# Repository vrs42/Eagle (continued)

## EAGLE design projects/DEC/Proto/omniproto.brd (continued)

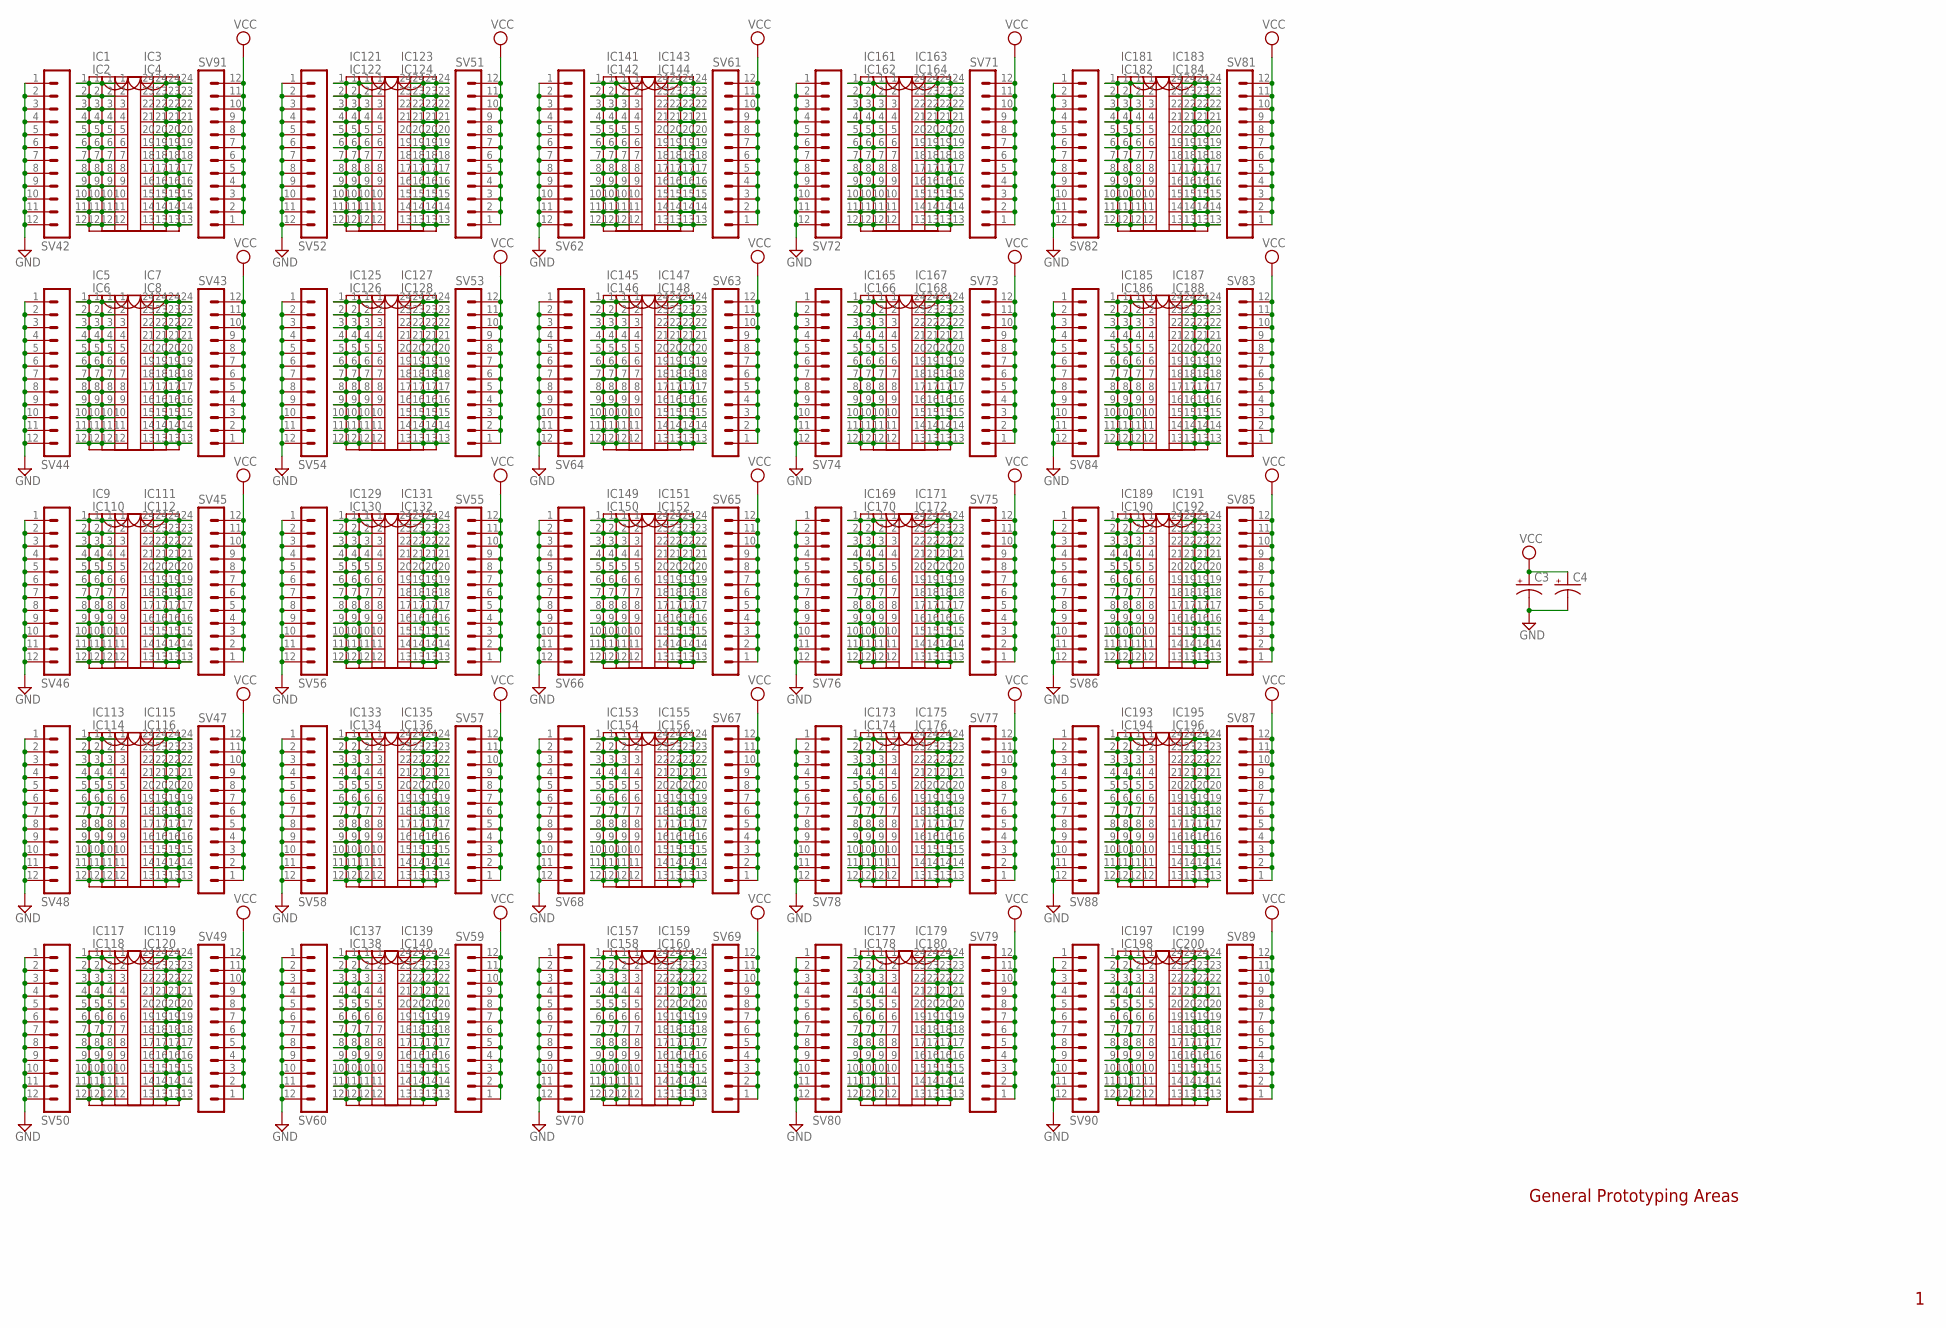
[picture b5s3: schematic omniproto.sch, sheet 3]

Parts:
C3, C4: CPOL-USE20-8AXIAL; E12-8
IC1, IC5, IC9, IC113, IC117, IC121, IC125, IC129, IC133, IC137, IC141, IC145, IC149, IC153, IC157, IC161, IC165, IC169, IC173, IC177, IC181, IC185, IC189, IC193, IC197: DIL24-3
IC2, IC4, IC6, IC8, IC110, IC112, IC114, IC116, IC118, IC120, IC122, IC124, IC126, IC128, IC130, IC132, IC134, IC136, IC138, IC140, IC142, IC144, IC146, IC148, IC150, IC152, IC154, IC156, IC158, IC160, IC162, IC164, IC166, IC168, IC170, IC172, IC174, IC176, IC178, IC180, IC182, IC184, IC186, IC188, IC190, IC192, IC194, IC196, IC198, IC200: DIL24-6
IC3, IC7, IC111, IC115, IC119, IC123, IC127, IC131, IC135, IC139, IC143, IC147, IC151, IC155, IC159, IC163, IC167, IC171, IC175, IC179, IC183, IC187, IC191, IC195, IC199: DIL24-9
SV42, SV43, SV44, SV45, SV46, SV47, SV48, SV49, SV50, SV51, SV52, SV53, SV54, SV55, SV56, SV57, SV58, SV59, SV60, SV61, SV62, SV63, SV64, SV65, SV66, SV67, SV68, SV69, SV70, SV71, SV72, SV73, SV74, SV75, SV76, SV77, SV78, SV79, SV80, SV81, SV82, SV83, SV84, SV85, SV86, SV87, SV88, SV89, SV90, SV91: MA12-1

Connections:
GND: C3.-, C4.-, SV42.1, SV42.2, SV42.3, SV42.4, SV42.5, SV42.6, SV42.7, SV42.8, SV42.9, SV42.10, SV42.11, SV42.12, SV44.1, SV44.2, SV44.3, SV44.4, SV44.5, SV44.6, SV44.7, SV44.8, SV44.9, SV44.10, SV44.11, SV44.12, SV46.1, SV46.2, SV46.3, SV46.4, SV46.5, SV46.6, SV46.7, SV46.8, SV46.9, SV46.10, SV46.11, SV46.12, SV48.1, SV48.2, SV48.3, SV48.4, SV48.5, SV48.6, SV48.7, SV48.8, SV48.9, SV48.10, SV48.11, SV48.12, SV50.1, SV50.2, SV50.3, SV50.4, SV50.5, SV50.6, SV50.7, SV50.8, SV50.9, SV50.10, SV50.11, SV50.12, SV52.1, SV52.2, SV52.3, SV52.4, SV52.5, SV52.6, SV52.7, SV52.8, SV52.9, SV52.10, SV52.11, SV52.12, SV54.1, SV54.2, SV54.3, SV54.4, SV54.5, SV54.6, SV54.7, SV54.8, SV54.9, SV54.10, SV54.11, SV54.12, SV56.1, SV56.2, SV56.3, SV56.4, SV56.5, SV56.6, SV56.7, SV56.8, SV56.9, SV56.10, SV56.11, SV56.12, SV58.1, SV58.2, SV58.3, SV58.4, SV58.5, SV58.6, SV58.7, SV58.8, SV58.9, SV58.10, SV58.11, SV58.12, SV60.1, SV60.2, SV60.3, SV60.4, SV60.5, SV60.6, SV60.7, SV60.8, SV60.9, SV60.10, SV60.11, SV60.12, SV62.1, SV62.2, SV62.3, SV62.4, SV62.5, SV62.6, SV62.7, SV62.8, SV62.9, SV62.10, SV62.11, SV62.12, SV64.1, SV64.2, SV64.3, SV64.4, SV64.5, SV64.6, SV64.7, SV64.8, SV64.9, SV64.10, SV64.11, SV64.12, SV66.1, SV66.2, SV66.3, SV66.4, SV66.5, SV66.6, SV66.7, SV66.8, SV66.9, SV66.10, SV66.11, SV66.12, SV68.1, SV68.2, SV68.3, SV68.4, SV68.5, SV68.6, SV68.7, SV68.8, SV68.9, SV68.10, SV68.11, SV68.12, SV70.1, SV70.2, SV70.3, SV70.4, SV70.5, SV70.6, SV70.7, SV70.8, SV70.9, SV70.10, SV70.11, SV70.12, SV72.1, SV72.2, SV72.3, SV72.4, SV72.5, SV72.6, SV72.7, SV72.8, SV72.9, SV72.10, SV72.11, SV72.12, SV74.1, SV74.2, SV74.3, SV74.4, SV74.5, SV74.6, SV74.7, SV74.8, SV74.9, SV74.10, SV74.11, SV74.12, SV76.1, SV76.2, SV76.3, SV76.4, SV76.5, SV76.6, SV76.7, SV76.8, SV76.9, SV76.10, SV76.11, SV76.12, SV78.1, SV78.2, SV78.3, SV78.4, SV78.5, SV78.6, SV78.7, SV78.8, SV78.9, SV78.10, SV78.11, SV78.12, SV80.1, SV80.2, SV80.3, SV80.4, SV80.5, SV80.6, SV80.7, SV80.8, SV80.9, SV80.10, SV80.11, SV80.12, SV82.1, SV82.2, SV82.3, SV82.4, SV82.5, SV82.6, SV82.7, SV82.8, SV82.9, SV82.10, SV82.11, SV82.12, SV84.1, SV84.2, SV84.3, SV84.4, SV84.5, SV84.6, SV84.7, SV84.8, SV84.9, SV84.10, SV84.11, SV84.12, SV86.1, SV86.2, SV86.3, SV86.4, SV86.5, SV86.6, SV86.7, SV86.8, SV86.9, SV86.10, SV86.11, SV86.12, SV88.1, SV88.2, SV88.3, SV88.4, SV88.5, SV88.6, SV88.7, SV88.8, SV88.9, SV88.10, SV88.11, SV88.12, SV90.1, SV90.2, SV90.3, SV90.4, SV90.5, SV90.6, SV90.7, SV90.8, SV90.9, SV90.10, SV90.11, SV90.12; also elsewhere on the board
unnamed: IC1.1, IC2.1, IC3.1, IC4.1
unnamed: IC1.2, IC2.2, IC3.2, IC4.2
unnamed: IC1.3, IC2.3, IC3.3, IC4.3
unnamed: IC1.4, IC2.4, IC3.4, IC4.4
unnamed: IC1.5, IC2.5, IC3.5, IC4.5
unnamed: IC1.6, IC2.6, IC3.6, IC4.6
unnamed: IC1.7, IC2.7, IC3.7, IC4.7
unnamed: IC1.8, IC2.8, IC3.8, IC4.8
unnamed: IC1.9, IC2.9, IC3.9, IC4.9
unnamed: IC1.10, IC2.10, IC3.10, IC4.10
unnamed: IC1.11, IC2.11, IC3.11, IC4.11
unnamed: IC1.12, IC2.12, IC3.12, IC4.12
unnamed: IC1.13, IC2.13, IC3.13, IC4.13
unnamed: IC1.14, IC2.14, IC3.14, IC4.14
unnamed: IC1.15, IC2.15, IC3.15, IC4.15
unnamed: IC1.16, IC2.16, IC3.16, IC4.16
unnamed: IC1.17, IC2.17, IC3.17, IC4.17
unnamed: IC1.18, IC2.18, IC3.18, IC4.18
unnamed: IC1.19, IC2.19, IC3.19, IC4.19
unnamed: IC1.20, IC2.20, IC3.20, IC4.20
unnamed: IC1.21, IC2.21, IC3.21, IC4.21
unnamed: IC1.22, IC2.22, IC3.22, IC4.22
unnamed: IC1.23, IC2.23, IC3.23, IC4.23
unnamed: IC1.24, IC2.24, IC3.24, IC4.24
unnamed: IC5.1, IC6.1, IC7.1, IC8.1
unnamed: IC5.2, IC6.2, IC7.2, IC8.2
unnamed: IC5.3, IC6.3, IC7.3, IC8.3
unnamed: IC5.4, IC6.4, IC7.4, IC8.4
unnamed: IC5.5, IC6.5, IC7.5, IC8.5
unnamed: IC5.6, IC6.6, IC7.6, IC8.6
unnamed: IC5.7, IC6.7, IC7.7, IC8.7
unnamed: IC5.8, IC6.8, IC7.8, IC8.8
unnamed: IC5.9, IC6.9, IC7.9, IC8.9
unnamed: IC5.10, IC6.10, IC7.10, IC8.10
unnamed: IC5.11, IC6.11, IC7.11, IC8.11
unnamed: IC5.12, IC6.12, IC7.12, IC8.12
unnamed: IC5.13, IC6.13, IC7.13, IC8.13
unnamed: IC5.14, IC6.14, IC7.14, IC8.14
unnamed: IC5.15, IC6.15, IC7.15, IC8.15
unnamed: IC5.16, IC6.16, IC7.16, IC8.16
unnamed: IC5.17, IC6.17, IC7.17, IC8.17
unnamed: IC5.18, IC6.18, IC7.18, IC8.18
unnamed: IC5.19, IC6.19, IC7.19, IC8.19
unnamed: IC5.20, IC6.20, IC7.20, IC8.20
unnamed: IC5.21, IC6.21, IC7.21, IC8.21
unnamed: IC5.22, IC6.22, IC7.22, IC8.22
unnamed: IC5.23, IC6.23, IC7.23, IC8.23
unnamed: IC5.24, IC6.24, IC7.24, IC8.24
unnamed: IC9.1, IC110.1, IC111.1, IC112.1
unnamed: IC9.2, IC110.2, IC111.2, IC112.2
unnamed: IC9.3, IC110.3, IC111.3, IC112.3
unnamed: IC9.4, IC110.4, IC111.4, IC112.4
unnamed: IC9.5, IC110.5, IC111.5, IC112.5
unnamed: IC9.6, IC110.6, IC111.6, IC112.6
unnamed: IC9.7, IC110.7, IC111.7, IC112.7
unnamed: IC9.8, IC110.8, IC111.8, IC112.8
unnamed: IC9.9, IC110.9, IC111.9, IC112.9
unnamed: IC9.10, IC110.10, IC111.10, IC112.10
unnamed: IC9.11, IC110.11, IC111.11, IC112.11
unnamed: IC9.12, IC110.12, IC111.12, IC112.12
unnamed: IC9.13, IC110.13, IC111.13, IC112.13
unnamed: IC9.14, IC110.14, IC111.14, IC112.14
unnamed: IC9.15, IC110.15, IC111.15, IC112.15
unnamed: IC9.16, IC110.16, IC111.16, IC112.16
unnamed: IC9.17, IC110.17, IC111.17, IC112.17
unnamed: IC9.18, IC110.18, IC111.18, IC112.18
unnamed: IC9.19, IC110.19, IC111.19, IC112.19
unnamed: IC9.20, IC110.20, IC111.20, IC112.20
unnamed: IC9.21, IC110.21, IC111.21, IC112.21
unnamed: IC9.22, IC110.22, IC111.22, IC112.22
unnamed: IC9.23, IC110.23, IC111.23, IC112.23
unnamed: IC9.24, IC110.24, IC111.24, IC112.24
unnamed: IC113.1, IC114.1, IC115.1, IC116.1
unnamed: IC113.2, IC114.2, IC115.2, IC116.2
unnamed: IC113.3, IC114.3, IC115.3, IC116.3
unnamed: IC113.4, IC114.4, IC115.4, IC116.4
unnamed: IC113.5, IC114.5, IC115.5, IC116.5
unnamed: IC113.6, IC114.6, IC115.6, IC116.6
unnamed: IC113.7, IC114.7, IC115.7, IC116.7
unnamed: IC113.8, IC114.8, IC115.8, IC116.8
unnamed: IC113.9, IC114.9, IC115.9, IC116.9
unnamed: IC113.10, IC114.10, IC115.10, IC116.10
unnamed: IC113.11, IC114.11, IC115.11, IC116.11
unnamed: IC113.12, IC114.12, IC115.12, IC116.12
unnamed: IC113.13, IC114.13, IC115.13, IC116.13
unnamed: IC113.14, IC114.14, IC115.14, IC116.14
unnamed: IC113.15, IC114.15, IC115.15, IC116.15
unnamed: IC113.16, IC114.16, IC115.16, IC116.16
unnamed: IC113.17, IC114.17, IC115.17, IC116.17
unnamed: IC113.18, IC114.18, IC115.18, IC116.18
unnamed: IC113.19, IC114.19, IC115.19, IC116.19
unnamed: IC113.20, IC114.20, IC115.20, IC116.20
unnamed: IC113.21, IC114.21, IC115.21, IC116.21
unnamed: IC113.22, IC114.22, IC115.22, IC116.22
unnamed: IC113.23, IC114.23, IC115.23, IC116.23
unnamed: IC113.24, IC114.24, IC115.24, IC116.24
unnamed: IC117.1, IC118.1, IC119.1, IC120.1
unnamed: IC117.2, IC118.2, IC119.2, IC120.2
unnamed: IC117.3, IC118.3, IC119.3, IC120.3
unnamed: IC117.4, IC118.4, IC119.4, IC120.4
unnamed: IC117.5, IC118.5, IC119.5, IC120.5
unnamed: IC117.6, IC118.6, IC119.6, IC120.6
unnamed: IC117.7, IC118.7, IC119.7, IC120.7
unnamed: IC117.8, IC118.8, IC119.8, IC120.8
unnamed: IC117.9, IC118.9, IC119.9, IC120.9
unnamed: IC117.10, IC118.10, IC119.10, IC120.10
unnamed: IC117.11, IC118.11, IC119.11, IC120.11
unnamed: IC117.12, IC118.12, IC119.12, IC120.12
unnamed: IC117.13, IC118.13, IC119.13, IC120.13
unnamed: IC117.14, IC118.14, IC119.14, IC120.14
unnamed: IC117.15, IC118.15, IC119.15, IC120.15
unnamed: IC117.16, IC118.16, IC119.16, IC120.16
unnamed: IC117.17, IC118.17, IC119.17, IC120.17
unnamed: IC117.18, IC118.18, IC119.18, IC120.18
unnamed: IC117.19, IC118.19, IC119.19, IC120.19
unnamed: IC117.20, IC118.20, IC119.20, IC120.20
unnamed: IC117.21, IC118.21, IC119.21, IC120.21
unnamed: IC117.22, IC118.22, IC119.22, IC120.22
unnamed: IC117.23, IC118.23, IC119.23, IC120.23
unnamed: IC117.24, IC118.24, IC119.24, IC120.24
unnamed: IC121.1, IC122.1, IC123.1, IC124.1
unnamed: IC121.2, IC122.2, IC123.2, IC124.2
unnamed: IC121.3, IC122.3, IC123.3, IC124.3
unnamed: IC121.4, IC122.4, IC123.4, IC124.4
unnamed: IC121.5, IC122.5, IC123.5, IC124.5
unnamed: IC121.6, IC122.6, IC123.6, IC124.6
unnamed: IC121.7, IC122.7, IC123.7, IC124.7
unnamed: IC121.8, IC122.8, IC123.8, IC124.8
unnamed: IC121.9, IC122.9, IC123.9, IC124.9
unnamed: IC121.10, IC122.10, IC123.10, IC124.10
unnamed: IC121.11, IC122.11, IC123.11, IC124.11
unnamed: IC121.12, IC122.12, IC123.12, IC124.12
unnamed: IC121.13, IC122.13, IC123.13, IC124.13
unnamed: IC121.14, IC122.14, IC123.14, IC124.14
unnamed: IC121.15, IC122.15, IC123.15, IC124.15
unnamed: IC121.16, IC122.16, IC123.16, IC124.16
unnamed: IC121.17, IC122.17, IC123.17, IC124.17
unnamed: IC121.18, IC122.18, IC123.18, IC124.18
unnamed: IC121.19, IC122.19, IC123.19, IC124.19
unnamed: IC121.20, IC122.20, IC123.20, IC124.20
unnamed: IC121.21, IC122.21, IC123.21, IC124.21
unnamed: IC121.22, IC122.22, IC123.22, IC124.22
unnamed: IC121.23, IC122.23, IC123.23, IC124.23
unnamed: IC121.24, IC122.24, IC123.24, IC124.24
unnamed: IC125.1, IC126.1, IC127.1, IC128.1
unnamed: IC125.2, IC126.2, IC127.2, IC128.2
unnamed: IC125.3, IC126.3, IC127.3, IC128.3
unnamed: IC125.4, IC126.4, IC127.4, IC128.4
unnamed: IC125.5, IC126.5, IC127.5, IC128.5
unnamed: IC125.6, IC126.6, IC127.6, IC128.6
unnamed: IC125.7, IC126.7, IC127.7, IC128.7
unnamed: IC125.8, IC126.8, IC127.8, IC128.8
unnamed: IC125.9, IC126.9, IC127.9, IC128.9
unnamed: IC125.10, IC126.10, IC127.10, IC128.10
unnamed: IC125.11, IC126.11, IC127.11, IC128.11
unnamed: IC125.12, IC126.12, IC127.12, IC128.12
unnamed: IC125.13, IC126.13, IC127.13, IC128.13
unnamed: IC125.14, IC126.14, IC127.14, IC128.14
unnamed: IC125.15, IC126.15, IC127.15, IC128.15
unnamed: IC125.16, IC126.16, IC127.16, IC128.16
unnamed: IC125.17, IC126.17, IC127.17, IC128.17
unnamed: IC125.18, IC126.18, IC127.18, IC128.18
unnamed: IC125.19, IC126.19, IC127.19, IC128.19
unnamed: IC125.20, IC126.20, IC127.20, IC128.20
unnamed: IC125.21, IC126.21, IC127.21, IC128.21
unnamed: IC125.22, IC126.22, IC127.22, IC128.22
unnamed: IC125.23, IC126.23, IC127.23, IC128.23
unnamed: IC125.24, IC126.24, IC127.24, IC128.24
unnamed: IC129.1, IC130.1, IC131.1, IC132.1
unnamed: IC129.2, IC130.2, IC131.2, IC132.2
unnamed: IC129.3, IC130.3, IC131.3, IC132.3
unnamed: IC129.4, IC130.4, IC131.4, IC132.4
unnamed: IC129.5, IC130.5, IC131.5, IC132.5
unnamed: IC129.6, IC130.6, IC131.6, IC132.6
unnamed: IC129.7, IC130.7, IC131.7, IC132.7
unnamed: IC129.8, IC130.8, IC131.8, IC132.8
unnamed: IC129.9, IC130.9, IC131.9, IC132.9
unnamed: IC129.10, IC130.10, IC131.10, IC132.10
unnamed: IC129.11, IC130.11, IC131.11, IC132.11
unnamed: IC129.12, IC130.12, IC131.12, IC132.12
unnamed: IC129.13, IC130.13, IC131.13, IC132.13
unnamed: IC129.14, IC130.14, IC131.14, IC132.14
unnamed: IC129.15, IC130.15, IC131.15, IC132.15
unnamed: IC129.16, IC130.16, IC131.16, IC132.16
unnamed: IC129.17, IC130.17, IC131.17, IC132.17
unnamed: IC129.18, IC130.18, IC131.18, IC132.18
unnamed: IC129.19, IC130.19, IC131.19, IC132.19
unnamed: IC129.20, IC130.20, IC131.20, IC132.20
unnamed: IC129.21, IC130.21, IC131.21, IC132.21
unnamed: IC129.22, IC130.22, IC131.22, IC132.22
unnamed: IC129.23, IC130.23, IC131.23, IC132.23
unnamed: IC129.24, IC130.24, IC131.24, IC132.24
unnamed: IC133.1, IC134.1, IC135.1, IC136.1
unnamed: IC133.2, IC134.2, IC135.2, IC136.2
unnamed: IC133.3, IC134.3, IC135.3, IC136.3
unnamed: IC133.4, IC134.4, IC135.4, IC136.4
unnamed: IC133.5, IC134.5, IC135.5, IC136.5
unnamed: IC133.6, IC134.6, IC135.6, IC136.6
unnamed: IC133.7, IC134.7, IC135.7, IC136.7
unnamed: IC133.8, IC134.8, IC135.8, IC136.8
unnamed: IC133.9, IC134.9, IC135.9, IC136.9
unnamed: IC133.10, IC134.10, IC135.10, IC136.10
unnamed: IC133.11, IC134.11, IC135.11, IC136.11
unnamed: IC133.12, IC134.12, IC135.12, IC136.12
unnamed: IC133.13, IC134.13, IC135.13, IC136.13
unnamed: IC133.14, IC134.14, IC135.14, IC136.14
unnamed: IC133.15, IC134.15, IC135.15, IC136.15
unnamed: IC133.16, IC134.16, IC135.16, IC136.16
unnamed: IC133.17, IC134.17, IC135.17, IC136.17
unnamed: IC133.18, IC134.18, IC135.18, IC136.18
unnamed: IC133.19, IC134.19, IC135.19, IC136.19
unnamed: IC133.20, IC134.20, IC135.20, IC136.20
unnamed: IC133.21, IC134.21, IC135.21, IC136.21
unnamed: IC133.22, IC134.22, IC135.22, IC136.22
unnamed: IC133.23, IC134.23, IC135.23, IC136.23
unnamed: IC133.24, IC134.24, IC135.24, IC136.24
unnamed: IC137.1, IC138.1, IC139.1, IC140.1
unnamed: IC137.2, IC138.2, IC139.2, IC140.2
unnamed: IC137.3, IC138.3, IC139.3, IC140.3
unnamed: IC137.4, IC138.4, IC139.4, IC140.4
unnamed: IC137.5, IC138.5, IC139.5, IC140.5
unnamed: IC137.6, IC138.6, IC139.6, IC140.6
unnamed: IC137.7, IC138.7, IC139.7, IC140.7
unnamed: IC137.8, IC138.8, IC139.8, IC140.8
unnamed: IC137.9, IC138.9, IC139.9, IC140.9
unnamed: IC137.10, IC138.10, IC139.10, IC140.10
unnamed: IC137.11, IC138.11, IC139.11, IC140.11
unnamed: IC137.12, IC138.12, IC139.12, IC140.12
unnamed: IC137.13, IC138.13, IC139.13, IC140.13
unnamed: IC137.14, IC138.14, IC139.14, IC140.14
unnamed: IC137.15, IC138.15, IC139.15, IC140.15
unnamed: IC137.16, IC138.16, IC139.16, IC140.16
unnamed: IC137.17, IC138.17, IC139.17, IC140.17
unnamed: IC137.18, IC138.18, IC139.18, IC140.18
unnamed: IC137.19, IC138.19, IC139.19, IC140.19
unnamed: IC137.20, IC138.20, IC139.20, IC140.20
unnamed: IC137.21, IC138.21, IC139.21, IC140.21
unnamed: IC137.22, IC138.22, IC139.22, IC140.22
unnamed: IC137.23, IC138.23, IC139.23, IC140.23
unnamed: IC137.24, IC138.24, IC139.24, IC140.24
unnamed: IC141.1, IC142.1, IC143.1, IC144.1
unnamed: IC141.2, IC142.2, IC143.2, IC144.2
unnamed: IC141.3, IC142.3, IC143.3, IC144.3
unnamed: IC141.4, IC142.4, IC143.4, IC144.4
unnamed: IC141.5, IC142.5, IC143.5, IC144.5
unnamed: IC141.6, IC142.6, IC143.6, IC144.6
unnamed: IC141.7, IC142.7, IC143.7, IC144.7
unnamed: IC141.8, IC142.8, IC143.8, IC144.8
unnamed: IC141.9, IC142.9, IC143.9, IC144.9
unnamed: IC141.10, IC142.10, IC143.10, IC144.10
unnamed: IC141.11, IC142.11, IC143.11, IC144.11
unnamed: IC141.12, IC142.12, IC143.12, IC144.12
unnamed: IC141.13, IC142.13, IC143.13, IC144.13
unnamed: IC141.14, IC142.14, IC143.14, IC144.14
unnamed: IC141.15, IC142.15, IC143.15, IC144.15
unnamed: IC141.16, IC142.16, IC143.16, IC144.16
unnamed: IC141.17, IC142.17, IC143.17, IC144.17
unnamed: IC141.18, IC142.18, IC143.18, IC144.18
unnamed: IC141.19, IC142.19, IC143.19, IC144.19
unnamed: IC141.20, IC142.20, IC143.20, IC144.20
unnamed: IC141.21, IC142.21, IC143.21, IC144.21
unnamed: IC141.22, IC142.22, IC143.22, IC144.22
unnamed: IC141.23, IC142.23, IC143.23, IC144.23
unnamed: IC141.24, IC142.24, IC143.24, IC144.24
unnamed: IC145.1, IC146.1, IC147.1, IC148.1
unnamed: IC145.2, IC146.2, IC147.2, IC148.2
unnamed: IC145.3, IC146.3, IC147.3, IC148.3
unnamed: IC145.4, IC146.4, IC147.4, IC148.4
unnamed: IC145.5, IC146.5, IC147.5, IC148.5
unnamed: IC145.6, IC146.6, IC147.6, IC148.6
unnamed: IC145.7, IC146.7, IC147.7, IC148.7
unnamed: IC145.8, IC146.8, IC147.8, IC148.8
unnamed: IC145.9, IC146.9, IC147.9, IC148.9
unnamed: IC145.10, IC146.10, IC147.10, IC148.10
unnamed: IC145.11, IC146.11, IC147.11, IC148.11
unnamed: IC145.12, IC146.12, IC147.12, IC148.12
unnamed: IC145.13, IC146.13, IC147.13, IC148.13
unnamed: IC145.14, IC146.14, IC147.14, IC148.14
unnamed: IC145.15, IC146.15, IC147.15, IC148.15
unnamed: IC145.16, IC146.16, IC147.16, IC148.16
unnamed: IC145.17, IC146.17, IC147.17, IC148.17
unnamed: IC145.18, IC146.18, IC147.18, IC148.18
unnamed: IC145.19, IC146.19, IC147.19, IC148.19
unnamed: IC145.20, IC146.20, IC147.20, IC148.20
unnamed: IC145.21, IC146.21, IC147.21, IC148.21
unnamed: IC145.22, IC146.22, IC147.22, IC148.22
unnamed: IC145.23, IC146.23, IC147.23, IC148.23
unnamed: IC145.24, IC146.24, IC147.24, IC148.24
unnamed: IC149.1, IC150.1, IC151.1, IC152.1
unnamed: IC149.2, IC150.2, IC151.2, IC152.2
unnamed: IC149.3, IC150.3, IC151.3, IC152.3
unnamed: IC149.4, IC150.4, IC151.4, IC152.4
unnamed: IC149.5, IC150.5, IC151.5, IC152.5
unnamed: IC149.6, IC150.6, IC151.6, IC152.6
unnamed: IC149.7, IC150.7, IC151.7, IC152.7
unnamed: IC149.8, IC150.8, IC151.8, IC152.8
unnamed: IC149.9, IC150.9, IC151.9, IC152.9
unnamed: IC149.10, IC150.10, IC151.10, IC152.10
unnamed: IC149.11, IC150.11, IC151.11, IC152.11
unnamed: IC149.12, IC150.12, IC151.12, IC152.12
unnamed: IC149.13, IC150.13, IC151.13, IC152.13
unnamed: IC149.14, IC150.14, IC151.14, IC152.14
unnamed: IC149.15, IC150.15, IC151.15, IC152.15
unnamed: IC149.16, IC150.16, IC151.16, IC152.16
unnamed: IC149.17, IC150.17, IC151.17, IC152.17
unnamed: IC149.18, IC150.18, IC151.18, IC152.18
unnamed: IC149.19, IC150.19, IC151.19, IC152.19
unnamed: IC149.20, IC150.20, IC151.20, IC152.20
unnamed: IC149.21, IC150.21, IC151.21, IC152.21
unnamed: IC149.22, IC150.22, IC151.22, IC152.22
unnamed: IC149.23, IC150.23, IC151.23, IC152.23
unnamed: IC149.24, IC150.24, IC151.24, IC152.24
unnamed: IC153.1, IC154.1, IC155.1, IC156.1
unnamed: IC153.2, IC154.2, IC155.2, IC156.2
unnamed: IC153.3, IC154.3, IC155.3, IC156.3
unnamed: IC153.4, IC154.4, IC155.4, IC156.4
unnamed: IC153.5, IC154.5, IC155.5, IC156.5
unnamed: IC153.6, IC154.6, IC155.6, IC156.6
unnamed: IC153.7, IC154.7, IC155.7, IC156.7
unnamed: IC153.8, IC154.8, IC155.8, IC156.8
unnamed: IC153.9, IC154.9, IC155.9, IC156.9
unnamed: IC153.10, IC154.10, IC155.10, IC156.10
unnamed: IC153.11, IC154.11, IC155.11, IC156.11
unnamed: IC153.12, IC154.12, IC155.12, IC156.12
unnamed: IC153.13, IC154.13, IC155.13, IC156.13
unnamed: IC153.14, IC154.14, IC155.14, IC156.14
unnamed: IC153.15, IC154.15, IC155.15, IC156.15
unnamed: IC153.16, IC154.16, IC155.16, IC156.16
unnamed: IC153.17, IC154.17, IC155.17, IC156.17
unnamed: IC153.18, IC154.18, IC155.18, IC156.18
unnamed: IC153.19, IC154.19, IC155.19, IC156.19
unnamed: IC153.20, IC154.20, IC155.20, IC156.20
unnamed: IC153.21, IC154.21, IC155.21, IC156.21
unnamed: IC153.22, IC154.22, IC155.22, IC156.22
unnamed: IC153.23, IC154.23, IC155.23, IC156.23
unnamed: IC153.24, IC154.24, IC155.24, IC156.24
unnamed: IC157.1, IC158.1, IC159.1, IC160.1
unnamed: IC157.2, IC158.2, IC159.2, IC160.2
unnamed: IC157.3, IC158.3, IC159.3, IC160.3
unnamed: IC157.4, IC158.4, IC159.4, IC160.4
unnamed: IC157.5, IC158.5, IC159.5, IC160.5
unnamed: IC157.6, IC158.6, IC159.6, IC160.6
unnamed: IC157.7, IC158.7, IC159.7, IC160.7
unnamed: IC157.8, IC158.8, IC159.8, IC160.8
unnamed: IC157.9, IC158.9, IC159.9, IC160.9
unnamed: IC157.10, IC158.10, IC159.10, IC160.10
unnamed: IC157.11, IC158.11, IC159.11, IC160.11
unnamed: IC157.12, IC158.12, IC159.12, IC160.12
unnamed: IC157.13, IC158.13, IC159.13, IC160.13
unnamed: IC157.14, IC158.14, IC159.14, IC160.14
unnamed: IC157.15, IC158.15, IC159.15, IC160.15
unnamed: IC157.16, IC158.16, IC159.16, IC160.16
unnamed: IC157.17, IC158.17, IC159.17, IC160.17
unnamed: IC157.18, IC158.18, IC159.18, IC160.18
unnamed: IC157.19, IC158.19, IC159.19, IC160.19
unnamed: IC157.20, IC158.20, IC159.20, IC160.20
unnamed: IC157.21, IC158.21, IC159.21, IC160.21
unnamed: IC157.22, IC158.22, IC159.22, IC160.22
unnamed: IC157.23, IC158.23, IC159.23, IC160.23
unnamed: IC157.24, IC158.24, IC159.24, IC160.24
unnamed: IC161.1, IC162.1, IC163.1, IC164.1
unnamed: IC161.2, IC162.2, IC163.2, IC164.2
unnamed: IC161.3, IC162.3, IC163.3, IC164.3
unnamed: IC161.4, IC162.4, IC163.4, IC164.4
unnamed: IC161.5, IC162.5, IC163.5, IC164.5
unnamed: IC161.6, IC162.6, IC163.6, IC164.6
unnamed: IC161.7, IC162.7, IC163.7, IC164.7
unnamed: IC161.8, IC162.8, IC163.8, IC164.8
unnamed: IC161.9, IC162.9, IC163.9, IC164.9
unnamed: IC161.10, IC162.10, IC163.10, IC164.10
unnamed: IC161.11, IC162.11, IC163.11, IC164.11
unnamed: IC161.12, IC162.12, IC163.12, IC164.12
unnamed: IC161.13, IC162.13, IC163.13, IC164.13
unnamed: IC161.14, IC162.14, IC163.14, IC164.14
unnamed: IC161.15, IC162.15, IC163.15, IC164.15
unnamed: IC161.16, IC162.16, IC163.16, IC164.16
unnamed: IC161.17, IC162.17, IC163.17, IC164.17
unnamed: IC161.18, IC162.18, IC163.18, IC164.18
unnamed: IC161.19, IC162.19, IC163.19, IC164.19
unnamed: IC161.20, IC162.20, IC163.20, IC164.20
unnamed: IC161.21, IC162.21, IC163.21, IC164.21
unnamed: IC161.22, IC162.22, IC163.22, IC164.22
unnamed: IC161.23, IC162.23, IC163.23, IC164.23
unnamed: IC161.24, IC162.24, IC163.24, IC164.24
unnamed: IC165.1, IC166.1, IC167.1, IC168.1
unnamed: IC165.2, IC166.2, IC167.2, IC168.2
unnamed: IC165.3, IC166.3, IC167.3, IC168.3
unnamed: IC165.4, IC166.4, IC167.4, IC168.4
unnamed: IC165.5, IC166.5, IC167.5, IC168.5
unnamed: IC165.6, IC166.6, IC167.6, IC168.6
unnamed: IC165.7, IC166.7, IC167.7, IC168.7
unnamed: IC165.8, IC166.8, IC167.8, IC168.8
unnamed: IC165.9, IC166.9, IC167.9, IC168.9
unnamed: IC165.10, IC166.10, IC167.10, IC168.10
unnamed: IC165.11, IC166.11, IC167.11, IC168.11
unnamed: IC165.12, IC166.12, IC167.12, IC168.12
unnamed: IC165.13, IC166.13, IC167.13, IC168.13
unnamed: IC165.14, IC166.14, IC167.14, IC168.14
unnamed: IC165.15, IC166.15, IC167.15, IC168.15
unnamed: IC165.16, IC166.16, IC167.16, IC168.16
unnamed: IC165.17, IC166.17, IC167.17, IC168.17
unnamed: IC165.18, IC166.18, IC167.18, IC168.18
unnamed: IC165.19, IC166.19, IC167.19, IC168.19
unnamed: IC165.20, IC166.20, IC167.20, IC168.20
unnamed: IC165.21, IC166.21, IC167.21, IC168.21
unnamed: IC165.22, IC166.22, IC167.22, IC168.22
unnamed: IC165.23, IC166.23, IC167.23, IC168.23
unnamed: IC165.24, IC166.24, IC167.24, IC168.24
unnamed: IC169.1, IC170.1, IC171.1, IC172.1
unnamed: IC169.2, IC170.2, IC171.2, IC172.2
unnamed: IC169.3, IC170.3, IC171.3, IC172.3
unnamed: IC169.4, IC170.4, IC171.4, IC172.4
unnamed: IC169.5, IC170.5, IC171.5, IC172.5
unnamed: IC169.6, IC170.6, IC171.6, IC172.6
unnamed: IC169.7, IC170.7, IC171.7, IC172.7
unnamed: IC169.8, IC170.8, IC171.8, IC172.8
unnamed: IC169.9, IC170.9, IC171.9, IC172.9
unnamed: IC169.10, IC170.10, IC171.10, IC172.10
unnamed: IC169.11, IC170.11, IC171.11, IC172.11
unnamed: IC169.12, IC170.12, IC171.12, IC172.12
unnamed: IC169.13, IC170.13, IC171.13, IC172.13
unnamed: IC169.14, IC170.14, IC171.14, IC172.14
unnamed: IC169.15, IC170.15, IC171.15, IC172.15
unnamed: IC169.16, IC170.16, IC171.16, IC172.16
unnamed: IC169.17, IC170.17, IC171.17, IC172.17
unnamed: IC169.18, IC170.18, IC171.18, IC172.18
unnamed: IC169.19, IC170.19, IC171.19, IC172.19
unnamed: IC169.20, IC170.20, IC171.20, IC172.20
unnamed: IC169.21, IC170.21, IC171.21, IC172.21
unnamed: IC169.22, IC170.22, IC171.22, IC172.22
unnamed: IC169.23, IC170.23, IC171.23, IC172.23
unnamed: IC169.24, IC170.24, IC171.24, IC172.24
unnamed: IC173.1, IC174.1, IC175.1, IC176.1
unnamed: IC173.2, IC174.2, IC175.2, IC176.2
unnamed: IC173.3, IC174.3, IC175.3, IC176.3
unnamed: IC173.4, IC174.4, IC175.4, IC176.4
unnamed: IC173.5, IC174.5, IC175.5, IC176.5
unnamed: IC173.6, IC174.6, IC175.6, IC176.6
unnamed: IC173.7, IC174.7, IC175.7, IC176.7
unnamed: IC173.8, IC174.8, IC175.8, IC176.8
unnamed: IC173.9, IC174.9, IC175.9, IC176.9
unnamed: IC173.10, IC174.10, IC175.10, IC176.10
unnamed: IC173.11, IC174.11, IC175.11, IC176.11
unnamed: IC173.12, IC174.12, IC175.12, IC176.12
unnamed: IC173.13, IC174.13, IC175.13, IC176.13
unnamed: IC173.14, IC174.14, IC175.14, IC176.14
unnamed: IC173.15, IC174.15, IC175.15, IC176.15
unnamed: IC173.16, IC174.16, IC175.16, IC176.16
unnamed: IC173.17, IC174.17, IC175.17, IC176.17
unnamed: IC173.18, IC174.18, IC175.18, IC176.18
unnamed: IC173.19, IC174.19, IC175.19, IC176.19
unnamed: IC173.20, IC174.20, IC175.20, IC176.20
unnamed: IC173.21, IC174.21, IC175.21, IC176.21
unnamed: IC173.22, IC174.22, IC175.22, IC176.22
unnamed: IC173.23, IC174.23, IC175.23, IC176.23
unnamed: IC173.24, IC174.24, IC175.24, IC176.24
unnamed: IC177.1, IC178.1, IC179.1, IC180.1
unnamed: IC177.2, IC178.2, IC179.2, IC180.2
unnamed: IC177.3, IC178.3, IC179.3, IC180.3
unnamed: IC177.4, IC178.4, IC179.4, IC180.4
unnamed: IC177.5, IC178.5, IC179.5, IC180.5
unnamed: IC177.6, IC178.6, IC179.6, IC180.6
unnamed: IC177.7, IC178.7, IC179.7, IC180.7
unnamed: IC177.8, IC178.8, IC179.8, IC180.8
unnamed: IC177.9, IC178.9, IC179.9, IC180.9
unnamed: IC177.10, IC178.10, IC179.10, IC180.10
unnamed: IC177.11, IC178.11, IC179.11, IC180.11
unnamed: IC177.12, IC178.12, IC179.12, IC180.12
unnamed: IC177.13, IC178.13, IC179.13, IC180.13
unnamed: IC177.14, IC178.14, IC179.14, IC180.14
unnamed: IC177.15, IC178.15, IC179.15, IC180.15
unnamed: IC177.16, IC178.16, IC179.16, IC180.16
unnamed: IC177.17, IC178.17, IC179.17, IC180.17
unnamed: IC177.18, IC178.18, IC179.18, IC180.18
unnamed: IC177.19, IC178.19, IC179.19, IC180.19
unnamed: IC177.20, IC178.20, IC179.20, IC180.20
unnamed: IC177.21, IC178.21, IC179.21, IC180.21
unnamed: IC177.22, IC178.22, IC179.22, IC180.22
unnamed: IC177.23, IC178.23, IC179.23, IC180.23
unnamed: IC177.24, IC178.24, IC179.24, IC180.24
unnamed: IC181.1, IC182.1, IC183.1, IC184.1
unnamed: IC181.2, IC182.2, IC183.2, IC184.2
unnamed: IC181.3, IC182.3, IC183.3, IC184.3
unnamed: IC181.4, IC182.4, IC183.4, IC184.4
unnamed: IC181.5, IC182.5, IC183.5, IC184.5
unnamed: IC181.6, IC182.6, IC183.6, IC184.6
unnamed: IC181.7, IC182.7, IC183.7, IC184.7
unnamed: IC181.8, IC182.8, IC183.8, IC184.8
unnamed: IC181.9, IC182.9, IC183.9, IC184.9
unnamed: IC181.10, IC182.10, IC183.10, IC184.10
unnamed: IC181.11, IC182.11, IC183.11, IC184.11
unnamed: IC181.12, IC182.12, IC183.12, IC184.12
unnamed: IC181.13, IC182.13, IC183.13, IC184.13
unnamed: IC181.14, IC182.14, IC183.14, IC184.14
unnamed: IC181.15, IC182.15, IC183.15, IC184.15
unnamed: IC181.16, IC182.16, IC183.16, IC184.16
unnamed: IC181.17, IC182.17, IC183.17, IC184.17
unnamed: IC181.18, IC182.18, IC183.18, IC184.18
unnamed: IC181.19, IC182.19, IC183.19, IC184.19
unnamed: IC181.20, IC182.20, IC183.20, IC184.20
unnamed: IC181.21, IC182.21, IC183.21, IC184.21
unnamed: IC181.22, IC182.22, IC183.22, IC184.22
unnamed: IC181.23, IC182.23, IC183.23, IC184.23
unnamed: IC181.24, IC182.24, IC183.24, IC184.24
unnamed: IC185.1, IC186.1, IC187.1, IC188.1
unnamed: IC185.2, IC186.2, IC187.2, IC188.2
unnamed: IC185.3, IC186.3, IC187.3, IC188.3
unnamed: IC185.4, IC186.4, IC187.4, IC188.4
unnamed: IC185.5, IC186.5, IC187.5, IC188.5
unnamed: IC185.6, IC186.6, IC187.6, IC188.6
unnamed: IC185.7, IC186.7, IC187.7, IC188.7
unnamed: IC185.8, IC186.8, IC187.8, IC188.8
unnamed: IC185.9, IC186.9, IC187.9, IC188.9
unnamed: IC185.10, IC186.10, IC187.10, IC188.10
unnamed: IC185.11, IC186.11, IC187.11, IC188.11
unnamed: IC185.12, IC186.12, IC187.12, IC188.12
unnamed: IC185.13, IC186.13, IC187.13, IC188.13
unnamed: IC185.14, IC186.14, IC187.14, IC188.14
unnamed: IC185.15, IC186.15, IC187.15, IC188.15
unnamed: IC185.16, IC186.16, IC187.16, IC188.16
unnamed: IC185.17, IC186.17, IC187.17, IC188.17
unnamed: IC185.18, IC186.18, IC187.18, IC188.18
unnamed: IC185.19, IC186.19, IC187.19, IC188.19
unnamed: IC185.20, IC186.20, IC187.20, IC188.20
unnamed: IC185.21, IC186.21, IC187.21, IC188.21
unnamed: IC185.22, IC186.22, IC187.22, IC188.22
unnamed: IC185.23, IC186.23, IC187.23, IC188.23
unnamed: IC185.24, IC186.24, IC187.24, IC188.24
unnamed: IC189.1, IC190.1, IC191.1, IC192.1
unnamed: IC189.2, IC190.2, IC191.2, IC192.2
unnamed: IC189.3, IC190.3, IC191.3, IC192.3
unnamed: IC189.4, IC190.4, IC191.4, IC192.4
unnamed: IC189.5, IC190.5, IC191.5, IC192.5
unnamed: IC189.6, IC190.6, IC191.6, IC192.6
unnamed: IC189.7, IC190.7, IC191.7, IC192.7
unnamed: IC189.8, IC190.8, IC191.8, IC192.8
unnamed: IC189.9, IC190.9, IC191.9, IC192.9
unnamed: IC189.10, IC190.10, IC191.10, IC192.10
unnamed: IC189.11, IC190.11, IC191.11, IC192.11
unnamed: IC189.12, IC190.12, IC191.12, IC192.12
unnamed: IC189.13, IC190.13, IC191.13, IC192.13
unnamed: IC189.14, IC190.14, IC191.14, IC192.14
unnamed: IC189.15, IC190.15, IC191.15, IC192.15
unnamed: IC189.16, IC190.16, IC191.16, IC192.16
unnamed: IC189.17, IC190.17, IC191.17, IC192.17
unnamed: IC189.18, IC190.18, IC191.18, IC192.18
unnamed: IC189.19, IC190.19, IC191.19, IC192.19
unnamed: IC189.20, IC190.20, IC191.20, IC192.20
unnamed: IC189.21, IC190.21, IC191.21, IC192.21
unnamed: IC189.22, IC190.22, IC191.22, IC192.22
unnamed: IC189.23, IC190.23, IC191.23, IC192.23
unnamed: IC189.24, IC190.24, IC191.24, IC192.24
unnamed: IC193.1, IC194.1, IC195.1, IC196.1
unnamed: IC193.2, IC194.2, IC195.2, IC196.2
unnamed: IC193.3, IC194.3, IC195.3, IC196.3
unnamed: IC193.4, IC194.4, IC195.4, IC196.4
unnamed: IC193.5, IC194.5, IC195.5, IC196.5
unnamed: IC193.6, IC194.6, IC195.6, IC196.6
unnamed: IC193.7, IC194.7, IC195.7, IC196.7
unnamed: IC193.8, IC194.8, IC195.8, IC196.8
unnamed: IC193.9, IC194.9, IC195.9, IC196.9
unnamed: IC193.10, IC194.10, IC195.10, IC196.10
unnamed: IC193.11, IC194.11, IC195.11, IC196.11
unnamed: IC193.12, IC194.12, IC195.12, IC196.12
unnamed: IC193.13, IC194.13, IC195.13, IC196.13
unnamed: IC193.14, IC194.14, IC195.14, IC196.14
unnamed: IC193.15, IC194.15, IC195.15, IC196.15
unnamed: IC193.16, IC194.16, IC195.16, IC196.16
unnamed: IC193.17, IC194.17, IC195.17, IC196.17
unnamed: IC193.18, IC194.18, IC195.18, IC196.18
unnamed: IC193.19, IC194.19, IC195.19, IC196.19
unnamed: IC193.20, IC194.20, IC195.20, IC196.20
unnamed: IC193.21, IC194.21, IC195.21, IC196.21
unnamed: IC193.22, IC194.22, IC195.22, IC196.22
unnamed: IC193.23, IC194.23, IC195.23, IC196.23
unnamed: IC193.24, IC194.24, IC195.24, IC196.24
unnamed: IC197.1, IC198.1, IC199.1, IC200.1
unnamed: IC197.2, IC198.2, IC199.2, IC200.2
unnamed: IC197.3, IC198.3, IC199.3, IC200.3
unnamed: IC197.4, IC198.4, IC199.4, IC200.4
unnamed: IC197.5, IC198.5, IC199.5, IC200.5
unnamed: IC197.6, IC198.6, IC199.6, IC200.6
unnamed: IC197.7, IC198.7, IC199.7, IC200.7
unnamed: IC197.8, IC198.8, IC199.8, IC200.8
unnamed: IC197.9, IC198.9, IC199.9, IC200.9
unnamed: IC197.10, IC198.10, IC199.10, IC200.10
unnamed: IC197.11, IC198.11, IC199.11, IC200.11
unnamed: IC197.12, IC198.12, IC199.12, IC200.12
unnamed: IC197.13, IC198.13, IC199.13, IC200.13
unnamed: IC197.14, IC198.14, IC199.14, IC200.14
unnamed: IC197.15, IC198.15, IC199.15, IC200.15
unnamed: IC197.16, IC198.16, IC199.16, IC200.16
unnamed: IC197.17, IC198.17, IC199.17, IC200.17
unnamed: IC197.18, IC198.18, IC199.18, IC200.18
unnamed: IC197.19, IC198.19, IC199.19, IC200.19
unnamed: IC197.20, IC198.20, IC199.20, IC200.20
unnamed: IC197.21, IC198.21, IC199.21, IC200.21
unnamed: IC197.22, IC198.22, IC199.22, IC200.22
unnamed: IC197.23, IC198.23, IC199.23, IC200.23
unnamed: IC197.24, IC198.24, IC199.24, IC200.24
VCC: C3.+, C4.+, SV43.1, SV43.2, SV43.3, SV43.4, SV43.5, SV43.6, SV43.7, SV43.8, SV43.9, SV43.10, SV43.11, SV43.12, SV45.1, SV45.2, SV45.3, SV45.4, SV45.5, SV45.6, SV45.7, SV45.8, SV45.9, SV45.10, SV45.11, SV45.12, SV47.1, SV47.2, SV47.3, SV47.4, SV47.5, SV47.6, SV47.7, SV47.8, SV47.9, SV47.10, SV47.11, SV47.12, SV49.1, SV49.2, SV49.3, SV49.4, SV49.5, SV49.6, SV49.7, SV49.8, SV49.9, SV49.10, SV49.11, SV49.12, SV51.1, SV51.2, SV51.3, SV51.4, SV51.5, SV51.6, SV51.7, SV51.8, SV51.9, SV51.10, SV51.11, SV51.12, SV53.1, SV53.2, SV53.3, SV53.4, SV53.5, SV53.6, SV53.7, SV53.8, SV53.9, SV53.10, SV53.11, SV53.12, SV55.1, SV55.2, SV55.3, SV55.4, SV55.5, SV55.6, SV55.7, SV55.8, SV55.9, SV55.10, SV55.11, SV55.12, SV57.1, SV57.2, SV57.3, SV57.4, SV57.5, SV57.6, SV57.7, SV57.8, SV57.9, SV57.10, SV57.11, SV57.12, SV59.1, SV59.2, SV59.3, SV59.4, SV59.5, SV59.6, SV59.7, SV59.8, SV59.9, SV59.10, SV59.11, SV59.12, SV61.1, SV61.2, SV61.3, SV61.4, SV61.5, SV61.6, SV61.7, SV61.8, SV61.9, SV61.10, SV61.11, SV61.12, SV63.1, SV63.2, SV63.3, SV63.4, SV63.5, SV63.6, SV63.7, SV63.8, SV63.9, SV63.10, SV63.11, SV63.12, SV65.1, SV65.2, SV65.3, SV65.4, SV65.5, SV65.6, SV65.7, SV65.8, SV65.9, SV65.10, SV65.11, SV65.12, SV67.1, SV67.2, SV67.3, SV67.4, SV67.5, SV67.6, SV67.7, SV67.8, SV67.9, SV67.10, SV67.11, SV67.12, SV69.1, SV69.2, SV69.3, SV69.4, SV69.5, SV69.6, SV69.7, SV69.8, SV69.9, SV69.10, SV69.11, SV69.12, SV71.1, SV71.2, SV71.3, SV71.4, SV71.5, SV71.6, SV71.7, SV71.8, SV71.9, SV71.10, SV71.11, SV71.12, SV73.1, SV73.2, SV73.3, SV73.4, SV73.5, SV73.6, SV73.7, SV73.8, SV73.9, SV73.10, SV73.11, SV73.12, SV75.1, SV75.2, SV75.3, SV75.4, SV75.5, SV75.6, SV75.7, SV75.8, SV75.9, SV75.10, SV75.11, SV75.12, SV77.1, SV77.2, SV77.3, SV77.4, SV77.5, SV77.6, SV77.7, SV77.8, SV77.9, SV77.10, SV77.11, SV77.12, SV79.1, SV79.2, SV79.3, SV79.4, SV79.5, SV79.6, SV79.7, SV79.8, SV79.9, SV79.10, SV79.11, SV79.12, SV81.1, SV81.2, SV81.3, SV81.4, SV81.5, SV81.6, SV81.7, SV81.8, SV81.9, SV81.10, SV81.11, SV81.12, SV83.1, SV83.2, SV83.3, SV83.4, SV83.5, SV83.6, SV83.7, SV83.8, SV83.9, SV83.10, SV83.11, SV83.12, SV85.1, SV85.2, SV85.3, SV85.4, SV85.5, SV85.6, SV85.7, SV85.8, SV85.9, SV85.10, SV85.11, SV85.12, SV87.1, SV87.2, SV87.3, SV87.4, SV87.5, SV87.6, SV87.7, SV87.8, SV87.9, SV87.10, SV87.11, SV87.12, SV89.1, SV89.2, SV89.3, SV89.4, SV89.5, SV89.6, SV89.7, SV89.8, SV89.9, SV89.10, SV89.11, SV89.12, SV91.1, SV91.2, SV91.3, SV91.4, SV91.5, SV91.6, SV91.7, SV91.8, SV91.9, SV91.10, SV91.11, SV91.12; also elsewhere on the board

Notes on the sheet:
General Prototyping Areas

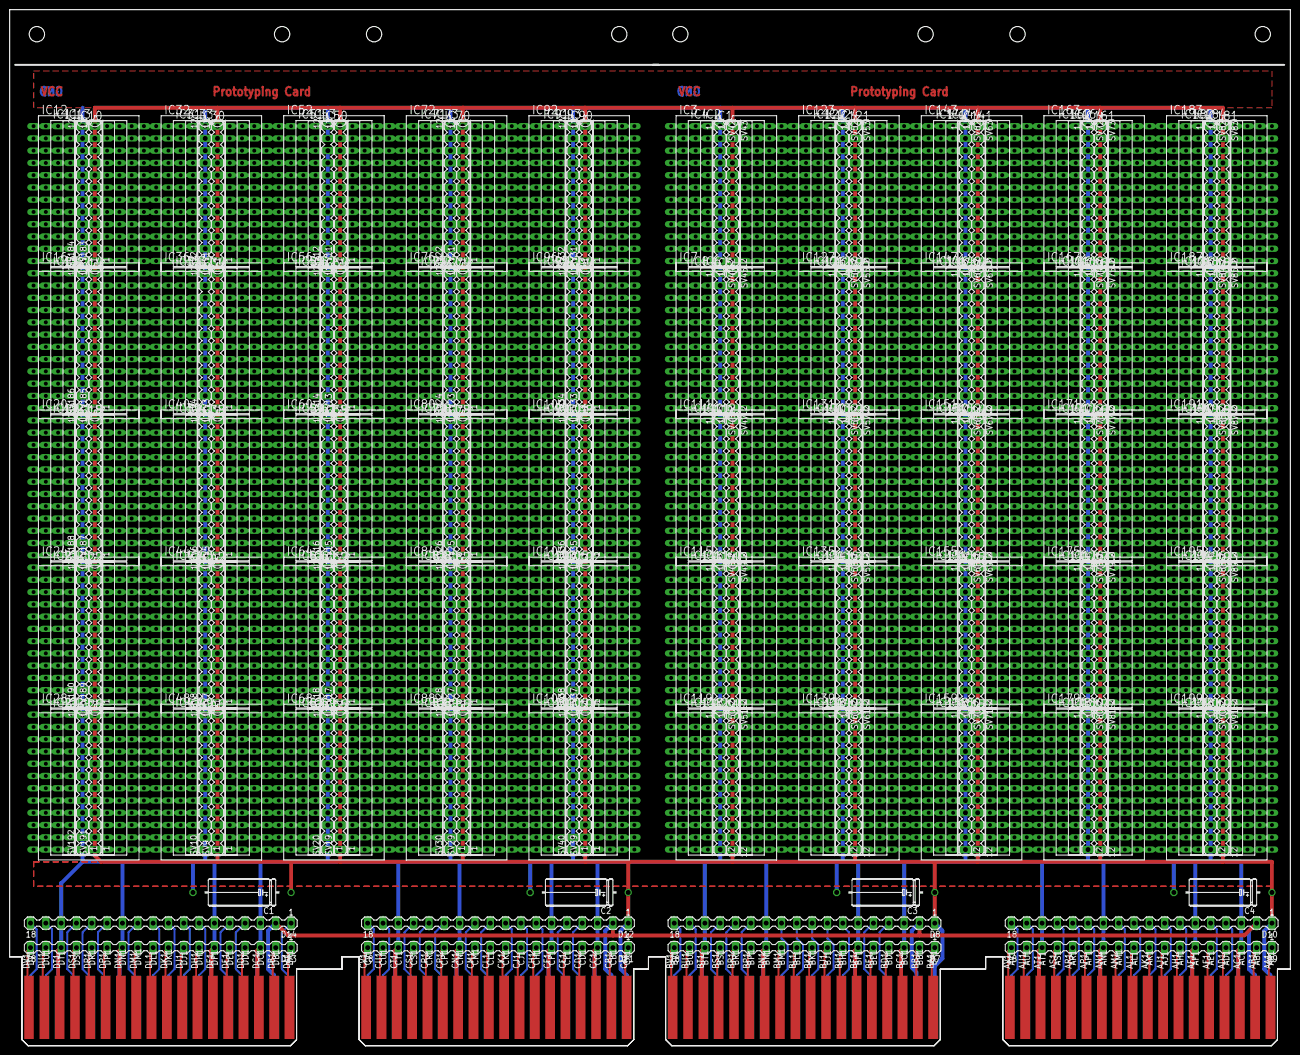
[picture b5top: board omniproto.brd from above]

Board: 2 copper layers, 265.3 x 214.6 mm, 314 parts (0 on the bottom side), 1308 nets.
